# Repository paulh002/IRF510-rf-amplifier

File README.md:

# IRF510-rf-amplifier

This amplifier was designed as a pspice simulation project. Later I have build and tested it.
The goal was to see if sources of distortion could be found and how certain components infuence the linearity of the amplifier.
In the simulation schematic extra components are added to simulate loss in the transformers. Changing these loss components give rise to more or less distrortion
There are 2 versions of the PCB in Kicad direcory IRF510 is used in RD16HFF directory the RD16HFF is used, this Fet has a different layout, so take care to choose the correct version.
With R6 and R11 you can control the gain. R9 and R14 are there to add extra stability. You can experiment with the values or make R9 and R14 0 ohm.

Small 10 to 20 Watt ampliefier (2 - 30 Mhz) with driver

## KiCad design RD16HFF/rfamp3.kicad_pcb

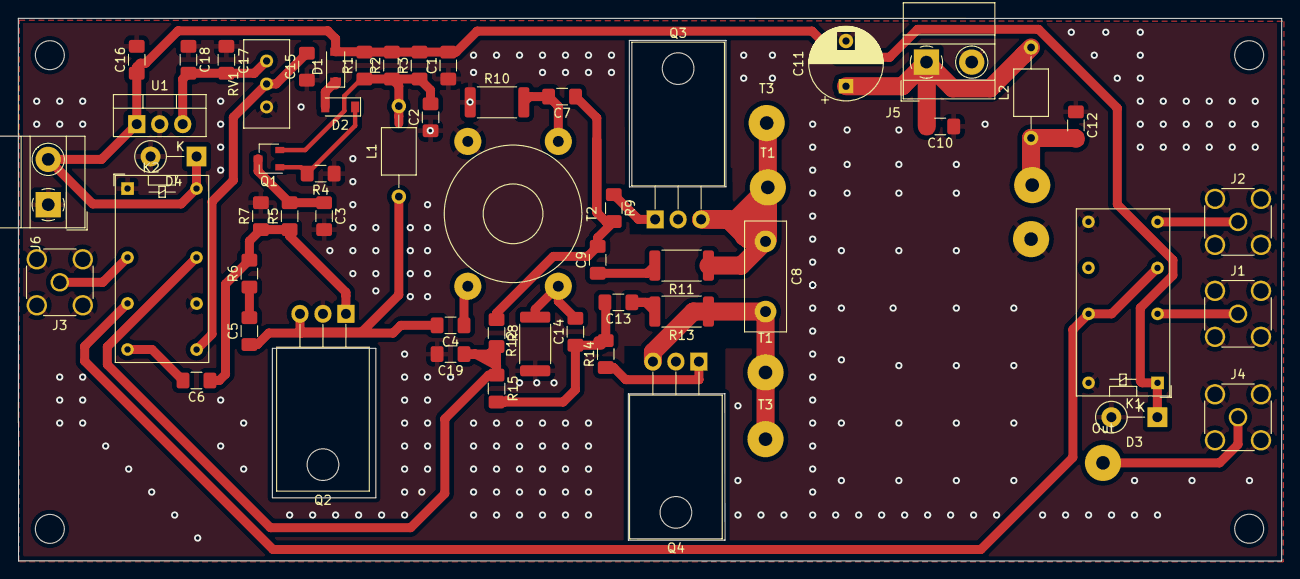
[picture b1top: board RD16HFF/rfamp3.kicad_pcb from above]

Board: 2 copper layers, 139.6 x 60.0 mm, 66 parts (0 on the bottom side), 31 nets.

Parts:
 : SolderWirePad_1x01_Drill1.5mm
 #2: SolderWirePad_1x01_Drill1.5mm
 #3,  #4,  #5,  #6: MountingHole_3.2mm_M3
C1, C2, C4, C5, C6, C7, C9, C10, C12, C13, C14, C15, C18, C19: 100n; C_1206_3216Metric_Pad1.42x1.75mm_HandSolder
C3: 1u; C_1206_3216Metric_Pad1.42x1.75mm_HandSolder
C8: 500p; C_Disc_D12.0mm_W4.4mm_P7.75mm
C11: 100u; CP_Radial_D8.0mm_P5.00mm
C16, C17: 10u; C_1206_3216Metric_Pad1.42x1.75mm_HandSolder
D1, D2: D; D_SOD-123
D3, D4: D; D_DO-41_SOD81_P5.08mm_Vertical_KathodeUp
J1, J3: Conn_Coaxial; SMA_Amphenol_132134_Vertical
J2: LPF-Out; SMA_Amphenol_132134_Vertical
J4: LPF; SMA_Amphenol_132134_Vertical
J5: 12V Power; TerminalBlock_MetzConnect_Type011_RT05502HBWC_1x02_P5.00mm_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
J6: 12V Switch; TerminalBlock_MetzConnect_Type011_RT05502HBWC_1x02_P5.00mm_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
K1, K2: G5V-2; Relay_DPDT_Omron_G5V-2
L1, L2: 100u; L_Axial_L5.0mm_D3.6mm_P10.00mm_Horizontal_Murata_BL01RN1A2A2
Out: SolderWirePad_1x01_Drill1.5mm
Q1: 2N3906; SOT-23W
Q2: RD06HHF; TO-220-3_Horizontal_TabDown
Q3: RD16HHF; TO-220-3_Horizontal_TabDown
Q4: RD16HFF; TO-220-3_Horizontal_TabDown
R1, R2, R3: 10; R_1206_3216Metric_Pad1.42x1.75mm_HandSolder
R4, R5, R7, R8, R15: 1k; R_1206_3216Metric_Pad1.42x1.75mm_HandSolder
R6: 560; R_1206_3216Metric_Pad1.42x1.75mm_HandSolder
R9, R14: 4.7; R_1206_3216Metric_Pad1.42x1.75mm_HandSolder
R10: 22; R_2512_6332Metric
R11, R13: 220; R_2512_6332Metric
R12: 10; R_2512_6332Metric
RV1: R_POT; Potentiometer_Bourns_3296W_Vertical
T1, T1#2, T3, T3#2: SolderWirePad_1x01_Drill1.5mm
T2: Transformer_1P_1S; Transformer_Toroid_Horizontal_D14.0mm_Amidon-T50
U1: L7805; TO-220-3_Vertical

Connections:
12V_Switch: C1.2, C16.1, D1.2 (A), D3.1 (K), D4.1 (K), J6.2, K1.1, K2.16, R1.2, R2.2, R3.2, U1.1 (IN)
Bias_A: C19.1, K2.13, R8.2, R15.1
GND: .1, C1.1, C2.1, C3.2, C10.1, C11.2, C12.1, C15.1, C16.2, C17.2, C18.1, C19.2, D3.2 (A), D4.2 (A), J1.2 (Ext), J2.2 (Ext), J3.2 (Ext), J4.2 (Ext), J5.2, J6.1, K1.9, K1.16, K2.1, K2.11, Q2.2 (S), Q3.2 (S), Q4.2 (S), R4.1, R7.2, R10.1, R12.1, RV1.3, T2.1 (AA), U1.2 (GND)
unnamed: C2.2, L1.2, Q1.2 (E), R1.1, R2.1, R3.1
unnamed: C3.1, Q1.3 (C), R5.2
unnamed: C4.1, T2.2 (AB)
unnamed: C4.2, C5.1, L1.1, Q2.3 (D)
unnamed: C5.2, R6.1
unnamed: C6.1, Q2.1 (G), R5.1, R6.2, R7.1
unnamed: C6.2, K2.8
unnamed: C7.1, C9.2, R8.1, R9.2
unnamed: C7.2, R10.2, T2.3 (SA)
unnamed: C8.1, Q3.3 (D), R11.1, T1#2.1, T3.1
unnamed: C8.2, Q4.3 (D), R13.1, T1.1, T3#2.1
unnamed: C9.1, R11.2
unnamed: C10.2, C11.1, J5.1, L2.2
unnamed: #2.1, C12.2, L2.1
unnamed: C13.1, R13.2
unnamed: C13.2, C14.1, R14.2, R15.2
unnamed: C14.2, R12.2, T2.4 (SB)
unnamed: C15.2, K2.9, RV1.2
unnamed: C17.1, C18.2, RV1.1, U1.3 (OUT)
unnamed: D1.1 (K), D2.2 (A)
unnamed: D2.1 (K), Q1.1 (B), R4.2
unnamed: J1.1 (In), K1.4
unnamed: J2.1 (In), K1.8
unnamed: J3.1 (In), K2.4
unnamed: J4.1 (In), Out.1
unnamed: K1.6, K1.13, K2.6
unnamed: Q3.1 (G), R9.1
unnamed: Q4.1 (G), R14.1

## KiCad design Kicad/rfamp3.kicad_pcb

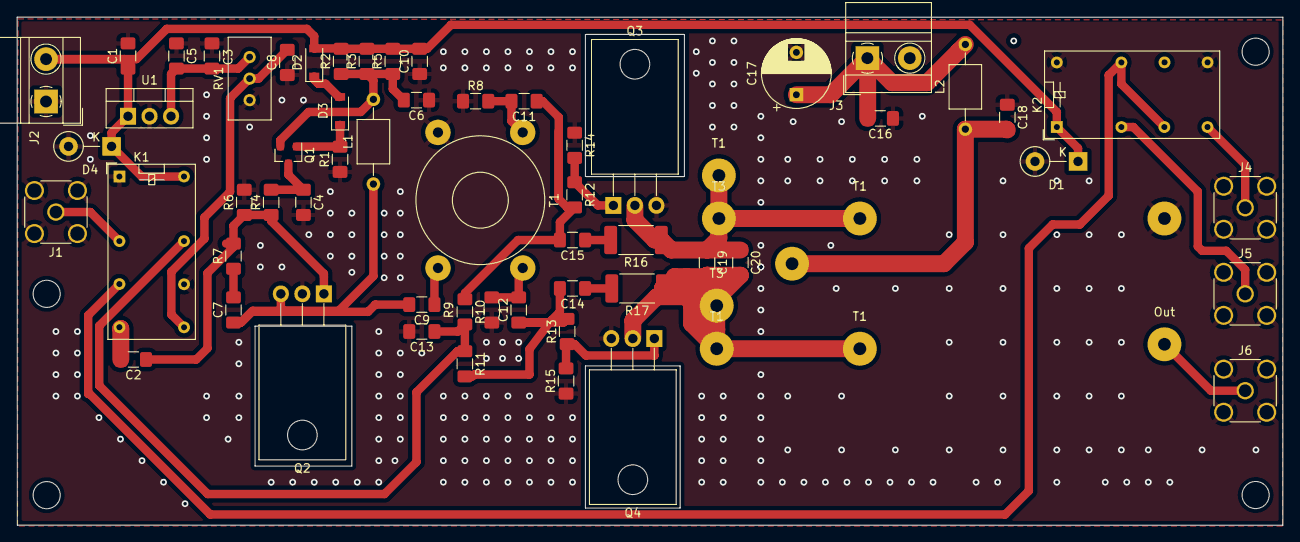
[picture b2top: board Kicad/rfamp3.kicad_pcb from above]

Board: 2 copper layers, 149.4 x 60.0 mm, 71 parts (0 on the bottom side), 32 nets.

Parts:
 : MountingHole_3.2mm_M3
 #2,  #3,  #4: MountingHole_3.2mm_M3
 #5,  #6: SolderWirePad_1x01_Drill1.5mm
C1, C3: 10u; C_1206_3216Metric_Pad1.42x1.75mm_HandSolder
C2, C5, C6, C7, C8, C9, C10, C11, C12, C13, C14, C15, C16, C18: 100n; C_1206_3216Metric_Pad1.42x1.75mm_HandSolder
C4: 1u; C_1206_3216Metric_Pad1.42x1.75mm_HandSolder
C17: 100u; CP_Radial_D8.0mm_P5.00mm
C19, C20: 500p; C_1206_3216Metric_Pad1.42x1.75mm_HandSolder
D1, D4: 1n4007; D_DO-41_SOD81_P5.08mm_Vertical_KathodeUp
D2, D3: D; D_SOD-123
J1, J5: Conn_Coaxial; SMA_Amphenol_132134_Vertical
J2: 12V Switch; TerminalBlock_MetzConnect_Type011_RT05502HBWC_1x02_P5.00mm_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
J3: 12V Power; TerminalBlock_MetzConnect_Type011_RT05502HBWC_1x02_P5.00mm_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
J4: LPF-Out; SMA_Amphenol_132134_Vertical
J6: LPF; SMA_Amphenol_132134_Vertical
K1, K2: G5V-2; Relay_DPDT_Omron_G5V-2
L1, L2: 100u; L_Axial_L5.0mm_D3.6mm_P10.00mm_Horizontal_Murata_BL01RN1A2A2
Out: SolderWirePad_1x01_Drill1.5mm
Q1: 2N3906; SOT-23
Q2: RD6HHF1; TO-220-3_Horizontal_TabDown
Q3, Q4: IRF510; TO-220-3_Horizontal_TabDown
R1, R4, R6, R10, R11, R14, R15: 1k; R_1206_3216Metric_Pad1.42x1.75mm_HandSolder
R2, R3, R5, R8, R9: 10; R_1206_3216Metric_Pad1.42x1.75mm_HandSolder
R7: 560; R_1206_3216Metric_Pad1.42x1.75mm_HandSolder
R12, R13: 1; R_1206_3216Metric_Pad1.42x1.75mm_HandSolder
R16, R17: 220; R_2512_6332Metric_Pad1.52x3.35mm_HandSolder
RV1: R_POT; Potentiometer_Bourns_3296W_Vertical
T1: Transformer_1P_1S; Transformer_Toroid_Horizontal_D14.0mm_Amidon-T50
T1#2, T1#3, T1#4, T1#5, T3, T3#2: SolderWirePad_1x01_Drill1.5mm
U1: L7805; TO-220-3_Vertical

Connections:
12V_Switch: C1.1, C10.2, D1.1 (K), D2.2 (A), D4.1 (K), J2.2, K1.16, K2.1, R2.2, R3.2, R5.2, U1.1 (IN)
Bias_A: C13.1, K1.13, R10.2, R11.1
GND: #5.1, C1.2, C3.2, C4.2, C5.1, C6.1, C8.1, C10.1, C13.2, C16.1, C17.2, C18.1, D1.2 (A), D4.2 (A), J1.2 (Ext), J2.1, J3.2, J4.2 (Ext), J5.2 (Ext), J6.2 (Ext), K1.1, K1.11, K2.9, K2.16, Q2.2 (S), Q3.3 (S), Q4.3 (S), R1.1, R6.2, R8.1, R9.1, R14.1, R15.1, RV1.3, T1.1 (AA), U1.2 (GND)
unnamed: C2.1, Q2.1 (G), R4.1, R6.1, R7.2
unnamed: C2.2, K1.8
unnamed: C3.1, C5.2, RV1.1, U1.3 (OUT)
unnamed: C4.1, Q1.3 (C), R4.2
unnamed: C6.2, L1.2, Q1.2 (E), R2.1, R3.1, R5.1
unnamed: C7.1, C9.2, L1.1, Q2.3 (D)
unnamed: C7.2, R7.1
unnamed: C8.2, K1.9, RV1.2
unnamed: C9.1, T1.2 (AB)
unnamed: C11.1, C15.2, R10.1, R12.2
unnamed: C11.2, R8.2, T1.3 (SA)
unnamed: C12.1, C14.2, R11.2, R13.2
unnamed: #6.1, C12.2, R9.2, T1.4 (SB)
unnamed: C14.1, R17.2
unnamed: C15.1, R16.2
unnamed: C16.2, C17.1, J3.1, L2.2
unnamed: C18.2, L2.1
unnamed: C19.1, C20.1, Q3.2 (D), R16.1
unnamed: C19.2, C20.2, Q4.2 (D), R17.1
unnamed: T1#3.1, T1#4.1, T3.1
unnamed: T1#2.1, T1#5.1, T3#2.1
unnamed: D2.1 (K), D3.2 (A)
unnamed: D3.1 (K), Q1.1 (B), R1.2
unnamed: J1.1 (In), K1.4
unnamed: J4.1 (In), K2.8, Out.1
unnamed: J5.1 (In), K2.4
unnamed: K1.6, K2.6, K2.13
unnamed: Q3.1 (G), R12.1, R14.2
unnamed: Q4.1 (G), R13.1, R15.2

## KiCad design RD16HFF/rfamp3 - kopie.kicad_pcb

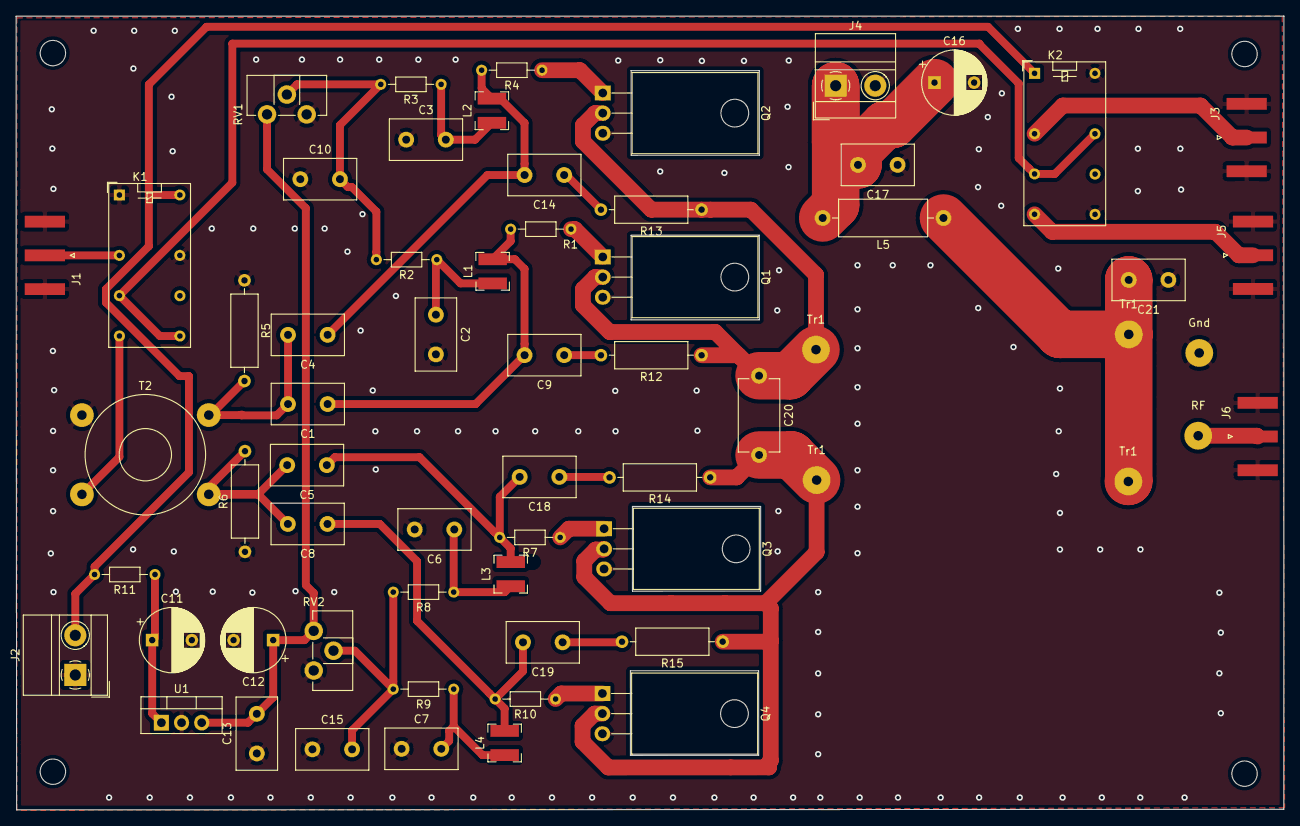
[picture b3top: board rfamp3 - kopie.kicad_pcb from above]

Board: 2 copper layers, 159.9 x 100.1 mm, 67 parts (0 on the bottom side), 34 nets.

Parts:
 : MountingHole_3.2mm_M3
 #2,  #3,  #4: MountingHole_3.2mm_M3
C1, C2, C3, C4, C5, C6, C7, C8, C9, C10, C13, C14, C15, C17, C18, C19, C21: 100n; C_Disc_D9.0mm_W5.0mm_P5.00mm
C11, C12: 10u; CP_Radial_D8.0mm_P5.00mm
C16: 100u; CP_Radial_D8.0mm_P5.00mm
C20: 500p; C_Disc_D9.0mm_W5.0mm_P10.00mm
Gnd: Gnd; SolderWirePad_1x01_Drill1.2mm
J1, J3: Conn_Coaxial; SMA_Amphenol_132289_EdgeMount
J2: 12V Switch; TerminalBlock_MetzConnect_Type011_RT05502HBWC_1x02_P5.00mm_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
J4: 12V Power; TerminalBlock_MetzConnect_Type011_RT05502HBWC_1x02_P5.00mm_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
J5: LPF-Out; SMA_Amphenol_132289_EdgeMount
J6: LPF; SMA_Amphenol_132289_EdgeMount
K1, K2: G5V-2; Relay_DPDT_Omron_G5V-2
L1, L2, L3, L4: 100u; L_Bourns-SRN4018
L5: 100u; L_Axial_L11.0mm_D4.5mm_P15.24mm_Horizontal_Fastron_MECC
Q1, Q2, Q3, Q4: IRFN24; TO-220-3_Horizontal_TabDown
R1, R4, R7, R10: 4.7; R_Axial_DIN0204_L3.6mm_D1.6mm_P7.62mm_Horizontal
R2, R3, R8, R9: 47; R_Axial_DIN0204_L3.6mm_D1.6mm_P7.62mm_Horizontal
R5, R6: 10; R_Axial_DIN0309_L9.0mm_D3.2mm_P12.70mm_Horizontal
R11: 2.2k; R_Axial_DIN0204_L3.6mm_D1.6mm_P7.62mm_Horizontal
R12, R13, R14, R15: 220; R_Axial_DIN0309_L9.0mm_D3.2mm_P12.70mm_Horizontal
RF: Rf; SolderWirePad_1x01_Drill1.2mm
RV1, RV2: R_POT; Potentiometer_ACP_CA9-H2,5_Horizontal
T2: Input transformer; Transformer_Toroid_Horizontal_D14.0mm_Amidon-T50
Tr1, Tr1#2, Tr1#3, Tr1#4: Tr1; SolderWirePad_1x01_Drill1.2mm
U1: L7805; TO-220-3_Vertical

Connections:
12V_Switch: J2.2, K1.16, K2.1, R11.2
Bias_A: C10.2, R2.2, R3.2, RV1.2
Bias_B: C15.2, R8.2, R9.2, RV2.2
GND: C2.2, C3.1, C6.2, C7.1, C10.1, C11.2, C12.2, C13.1, C15.1, C16.2, C17.1, C21.1, Gnd.1, J1.2, J2.1, J3.2, J4.2, J5.2, J6.2, K1.1, K1.13, K2.9, K2.16, Q1.3, Q2.3, Q3.3, Q4.3, R5.1, R6.1, RV1.3, RV2.3, T2.3, U1.2
unnamed: C1.1, C9.2, L1.1, R1.2
unnamed: C1.2, C4.2, R5.2, T2.4
unnamed: C2.1, L1.2, R2.1
unnamed: C3.2, L2.2, R3.1
unnamed: C5.2, C8.2, R6.2, T2.2
unnamed: C6.1, L3.2, R8.1
unnamed: C7.2, L4.2, R9.1
unnamed: C9.1, R12.2
unnamed: C11.1, R11.1, U1.1
unnamed: C12.1, C13.2, RV1.1, RV2.1, U1.3
unnamed: C14.1, R13.2
unnamed: C4.1, C14.2, L2.1, R4.2
unnamed: C16.1, C17.2, J4.1, L5.2
unnamed: C18.1, R14.2
unnamed: C5.1, C18.2, L3.1, R7.2
unnamed: C19.1, R15.2
unnamed: C8.1, C19.2, L4.1, R10.2
unnamed: C20.1, Q1.2, Q2.2, R12.1, R13.1, Tr1#2.1
unnamed: C20.2, Q3.2, Q4.2, R14.1, R15.1, Tr1.1
unnamed: C21.2, L5.1, Tr1#3.1, Tr1#4.1
unnamed: J1.1, K1.4
unnamed: J3.1, K2.4
unnamed: J5.1, K2.8
unnamed: J6.1, RF.1
unnamed: K1.6, K1.9, K2.6, K2.13
unnamed: K1.8, T2.1
unnamed: Q1.1, R1.1
unnamed: Q2.1, R4.1
unnamed: Q3.1, R7.1
unnamed: Q4.1, R10.1

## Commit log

2022-06-01 add fly back diode
2022-11-03 add RD16HFF version
